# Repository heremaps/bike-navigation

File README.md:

# This repository has been archived!

The current version of the HERE WeGo app on Android does not support BLE devices anymore.

# BikeNavigation

The bike navigation project was born out of the HERE maker lab in Berlin. A group of employees volunteered their time to build a companion device that connects to the HERE app on Android, including an open-source toolkit to build a custom bike navigation device.

## License

Unless otherwise noted in `LICENSE` files for specific files or directories, the [LICENSE](LICENSE) in the root applies to all content in this repository.

## Directory Contents

* *arduino*: Codes implementing BikeNavigation BLE profile
* *ble_specs*: Documentation describing BikeNavigation BLE profile
* *board*: PCB Design files for BikeNavigation
* *enclosure*: 3d and acrylic cases for BikeNavigation

## Disclaimer

You are required to provide the end-user of the device with the following notice prior to use and are responsible to localize this notice according to local laws: “Focus on the traffic when using the device - your first consideration while using the device in traffic has to be safety.”

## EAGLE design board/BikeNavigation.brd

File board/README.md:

# BikeNavigation

## BikeNavigation PCB & schematic

The board and the schematic are designed with [CadSoft EAGLE](http://www.cadsoftusa.com/eagle-pcb-design-software/about-eagle/). To work with the files you need at least EAGLE version 6.

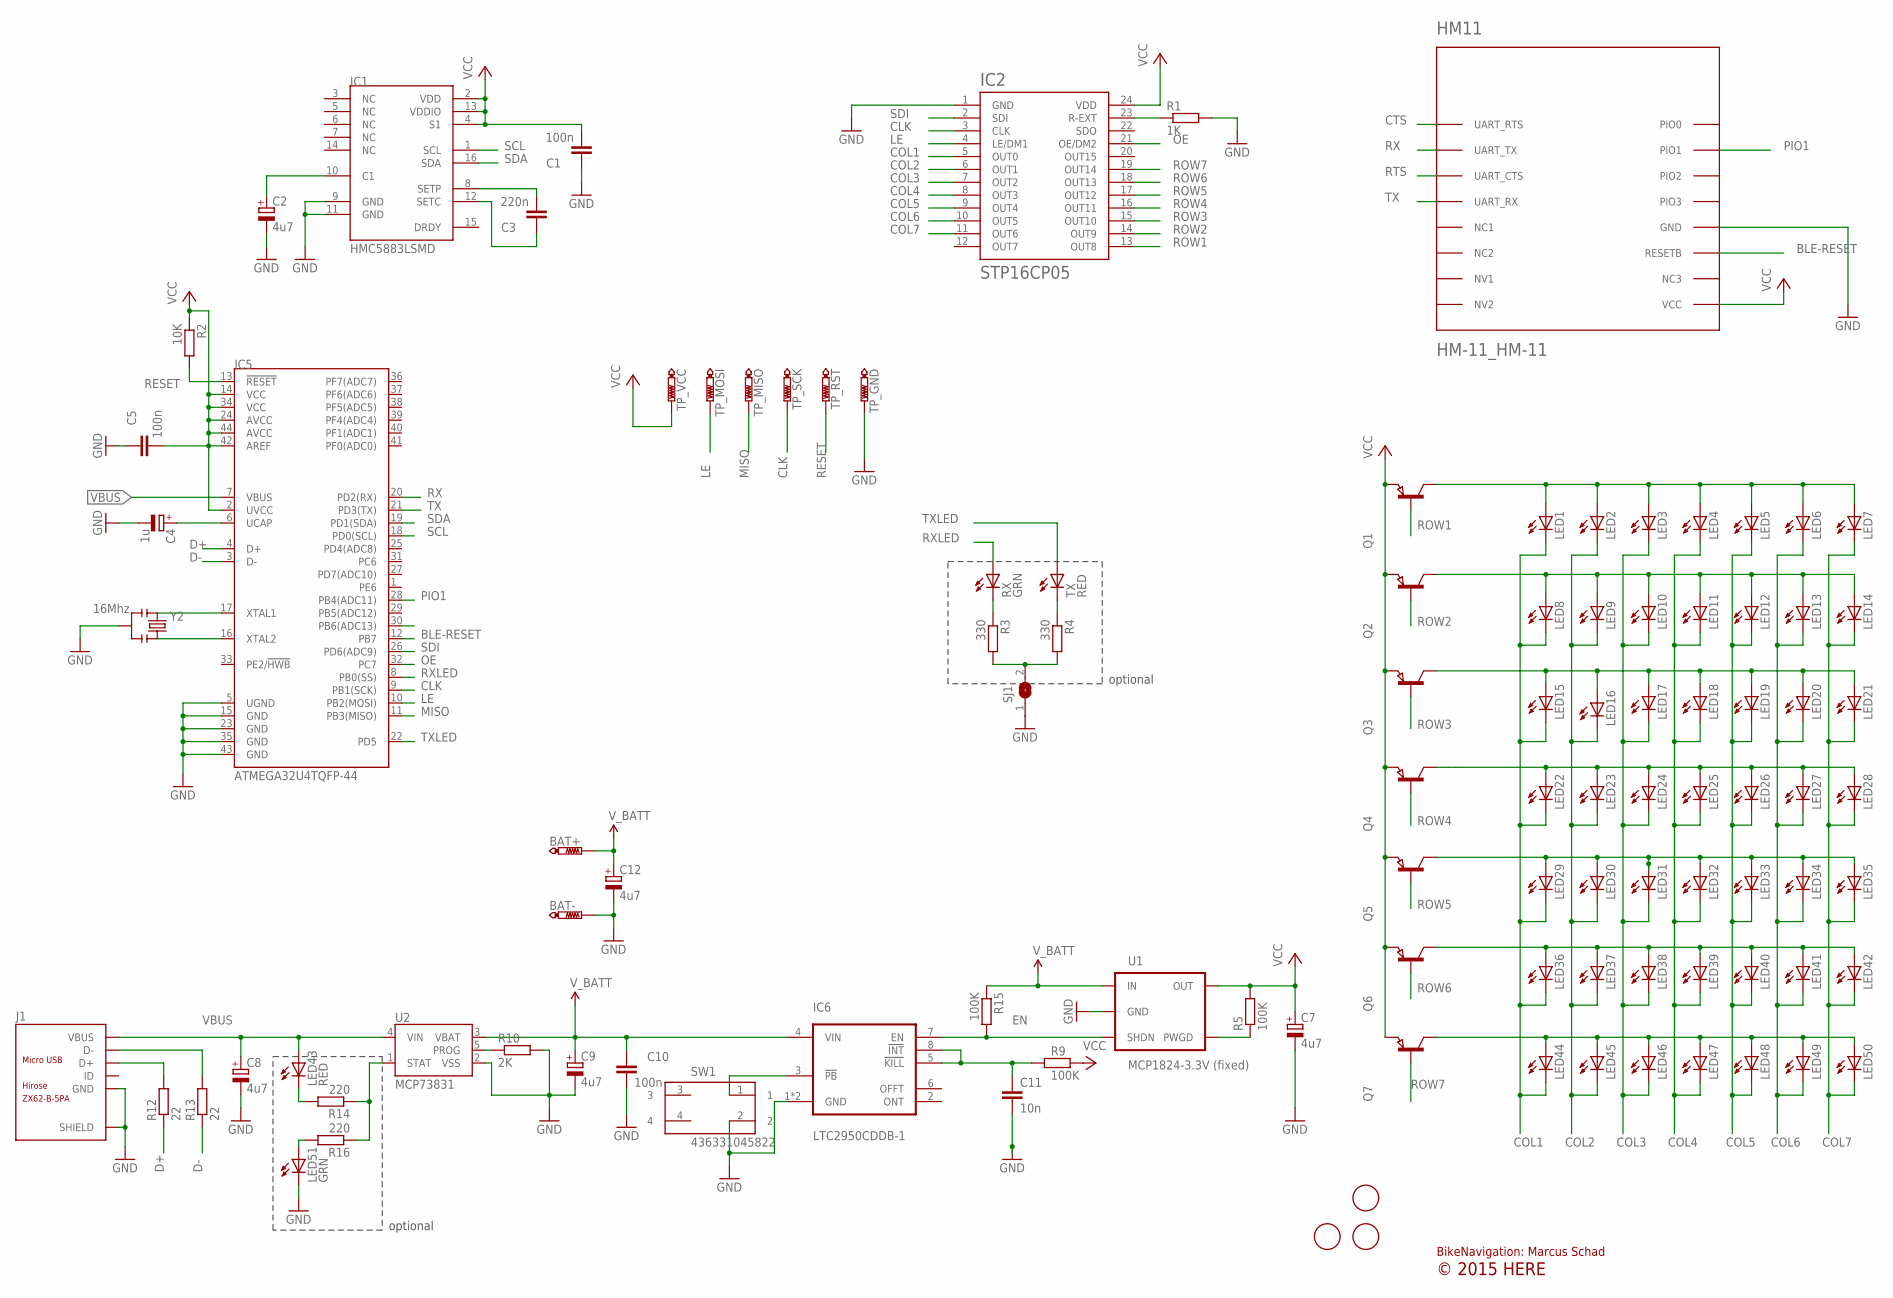
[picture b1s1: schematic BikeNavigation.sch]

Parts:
BAT+: PTR1TP20SQ; TP20SQ
BAT-: PTR1TP20SQ; TP20SQ
C1, C5, C10: 100n; C0402; PARTNO 445-3445-1-ND
C2, C7, C8, C9, C12: 4u7; SMC_A
C3: 220n; C0402; PARTNO 445-3445-1-ND
C4: 1u; SMC_A
C11: 10n; C0402; PARTNO 445-1260-1-ND
HM11: HM-11_HM-11
IC1: HMC5883LSMD; 16LPCC
IC2: STP16CP05; TSSOP24
IC5: ATMEGA32U4TQFP-44; TQFP44
IC6: LTC2950CDDB-1; DDB-8; PARTNO LTC2950IDDB-1#TRMPBFCT-ND
J1: MICRO-USB-SMD(ZX62-B-5PA); MICRO-USB5+6P-SMD-0.65-AB
LED1, LED2, LED3, LED4, LED5, LED6, LED7, LED8, LED9, LED10, LED11, LED12, LED13, LED14, LED15, LED16, LED17, LED18, LED19, LED20, LED21, LED22, LED23, LED24, LED25, LED26, LED27, LED28, LED29, LED30, LED31, LED32, LED33, LED34, LED35, LED36, LED37, LED38, LED39, LED40, LED41, LED42, LED44, LED45, LED46, LED47, LED48, LED49, LED50: LEDCHIP-LED0603; CHIP-LED0603
LED43: RED; SML0805
LED51: GRN; SML0805
Q1, Q2, Q3, Q4, Q5, Q6, Q7: PNP-TRANSISTOR_SOT23; SOT23
R1: 1K; R0402
R2: 10K; R0402
R3, R4: 330; R0402
R5: 100K; R0402
R9: 100K; R0402; PARTNO P510KJCT-ND
R10: 2K; R0402
R12, R13: 22; R0402
R14, R16: 220; R0402
R15: 100K; R0402; PARTNO P100KJCT-ND
RX: GRN; CHIP-LED0603
SJ1: SJ
SW1: 436331045822
TP_GND: PTR1TP20SQ; TP20SQ
TP_MISO: PTR1TP20SQ; TP20SQ
TP_MOSI: PTR1TP20SQ; TP20SQ
TP_RST: PTR1TP20SQ; TP20SQ
TP_SCK: PTR1TP20SQ; TP20SQ
TP_VCC: PTR1TP20SQ; TP20SQ
TX: RED; CHIP-LED0603
U1: MCP1824-3.3V (fixed); SOT23-5
U2: MCP73831; SOT23-5
U$1, U$2, U$3: FIDUCIAL; FIDUCIAL_1MM
Y2: 16Mhz; RESONATOR-SMD; PARTNO *

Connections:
$NS100: LED1.A, LED2.A, LED3.A, LED4.A, LED5.A, LED6.A, LED7.A, Q1.3 (C)
$NS101: LED8.A, LED9.A, LED10.A, LED11.A, LED12.A, LED13.A, LED14.A, Q2.3 (C)
$NS102: LED15.A, LED16.A, LED17.A, LED18.A, LED19.A, LED20.A, LED21.A, Q3.3 (C)
$NS104: LED22.A, LED23.A, LED24.A, LED25.A, LED26.A, LED27.A, LED28.A, Q4.3 (C)
$NS105: LED29.A, LED30.A, LED31.A, LED32.A, LED33.A, LED34.A, LED35.A, Q5.3 (C)
$NS107: LED36.A, LED37.A, LED38.A, LED39.A, LED40.A, LED41.A, LED42.A, Q6.3 (C)
$NS109: LED44.A, LED45.A, LED46.A, LED47.A, LED48.A, LED49.A, LED50.A, Q7.3 (C)
BLE-RESET: HM11.RESETB, IC5.12 (PB7)
CLK: IC2.3 (CLK), IC5.9 (PB1(SCK)), TP_SCK.TP
COL1: IC2.5 (OUT0), LED1.C, LED8.C, LED15.C, LED22.C, LED29.C, LED36.C, LED44.C
COL2: IC2.6 (OUT1), LED2.C, LED9.C, LED16.C, LED23.C, LED30.C, LED37.C, LED45.C
COL3: IC2.7 (OUT2), LED3.C, LED10.C, LED17.C, LED24.C, LED31.C, LED38.C, LED46.C
COL4: IC2.8 (OUT3), LED4.C, LED11.C, LED18.C, LED25.C, LED32.C, LED39.C, LED47.C
COL5: IC2.9 (OUT4), LED5.C, LED12.C, LED19.C, LED26.C, LED33.C, LED40.C, LED48.C
COL6: IC2.10 (OUT5), LED6.C, LED13.C, LED20.C, LED27.C, LED34.C, LED41.C, LED49.C
COL7: IC2.11 (OUT6), LED7.C, LED14.C, LED21.C, LED28.C, LED35.C, LED42.C, LED50.C
CTS: HM11.UART_RTS
D+: IC5.4 (D+), R12.1
D-: IC5.3 (D-), R13.1
EN: IC6.7 (EN), R15.2, U1.3 (SHDN)
GND: BAT-.TP, C1.1, C2.-, C4.-, C5.1, C7.-, C8.-, C9.-, C10.2, C11.2, C12.-, HM11.GND, IC1.9 (GND), IC1.11 (GND), IC2.1 (GND), IC5.5 (UGND), IC5.15 (GND), IC5.23 (GND), IC5.35 (GND), IC5.43 (GND), IC6.1 (GND), IC6.TPAD (GND), J1.5 (GND), J1.P1 (SHIELD), J1.P2 (SHIELD), J1.P3 (SHIELD), J1.P4 (SHIELD), J1.P5 (SHIELD), J1.P6 (SHIELD), LED51.C, R1.2, R10.2, SJ1.1, SW1.2, TP_GND.TP, U1.2 (GND), U2.2 (VSS), Y2.2
LE: IC2.4 (LE/DM1), IC5.10 (PB2(MOSI)), TP_MOSI.TP
MISO: IC5.11 (PB3(MISO)), TP_MISO.TP
unnamed: R5.1, U1.4 (PWGD)
unnamed: R3.1, RX.C
unnamed: R4.1, TX.C
unnamed: IC2.23 (R-EXT), R1.1
unnamed: R3.2, R4.2, SJ1.2
unnamed: C4.+, IC5.6 (UCAP)
unnamed: LED43.C, R14.2
unnamed: LED51.A, R16.2
unnamed: J1.3 (D+), R12.2
unnamed: C2.+, IC1.10 (C1)
unnamed: J1.2 (D-), R13.2
unnamed: IC6.3 (!PB), SW1.1
unnamed: C11.1, IC6.5 (!KILL), IC6.8 (!INT), R9.1
unnamed: C3.2, IC1.8 (SETP)
unnamed: C3.1, IC1.12 (SETC)
OE: IC2.21 (OE/DM2), IC5.32 (PC7)
PIO1: HM11.PIO1, IC5.28 (PB4(ADC11))
PROG: R10.1, U2.5 (PROG)
RESET: IC5.13 (!RESET), R2.2, TP_RST.TP
ROW1: IC2.13 (OUT8), Q1.1 (B)
ROW2: IC2.14 (OUT9), Q2.1 (B)
ROW3: IC2.15 (OUT10), Q3.1 (B)
ROW4: IC2.16 (OUT11), Q4.1 (B)
ROW5: IC2.17 (OUT12), Q5.1 (B)
ROW6: IC2.18 (OUT13), Q6.1 (B)
ROW7: IC2.19 (OUT14), Q7.1 (B)
RTS: HM11.UART_CTS
RX: HM11.UART_TX, IC5.20 (PD2(RX))
RXLED: IC5.8 (PB0(SS)), RX.A
SCL: IC1.1 (SCL), IC5.18 (PD0(SCL))
SDA: IC1.16 (SDA), IC5.19 (PD1(SDA))
SDI: IC2.2 (SDI), IC5.26 (PD6(ADC9))
STAT: R14.1, R16.1, U2.1 (STAT)
TX: HM11.UART_RX, IC5.21 (PD3(TX))
TXLED: IC5.22 (PD5), TX.A
VBUS: C8.+, IC5.7 (VBUS), J1.1 (VBUS), LED43.A, U2.4 (VIN)
VCC: C1.2, C5.2, C7.+, HM11.VCC, IC1.2 (VDD), IC1.4 (S1), IC1.13 (VDDIO), IC2.24 (VDD), IC5.2 (UVCC), IC5.14 (VCC), IC5.24 (AVCC), IC5.34 (VCC), IC5.42 (AREF), IC5.44 (AVCC), Q1.2 (E), Q2.2 (E), Q3.2 (E), Q4.2 (E), Q5.2 (E), Q6.2 (E), Q7.2 (E), R2.1, R5.2, R9.2, TP_VCC.TP, U1.5 (OUT)
V_BATT: BAT+.TP, C9.+, C10.1, C12.+, IC6.4 (VIN), R15.1, U1.1 (IN), U2.3 (VBAT)
XTAL1: IC5.17 (XTAL1), Y2.1
XTAL2: IC5.16 (XTAL2), Y2.3

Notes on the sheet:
BikeNavigation: Marcus Schad
optional
© 2015 HERE

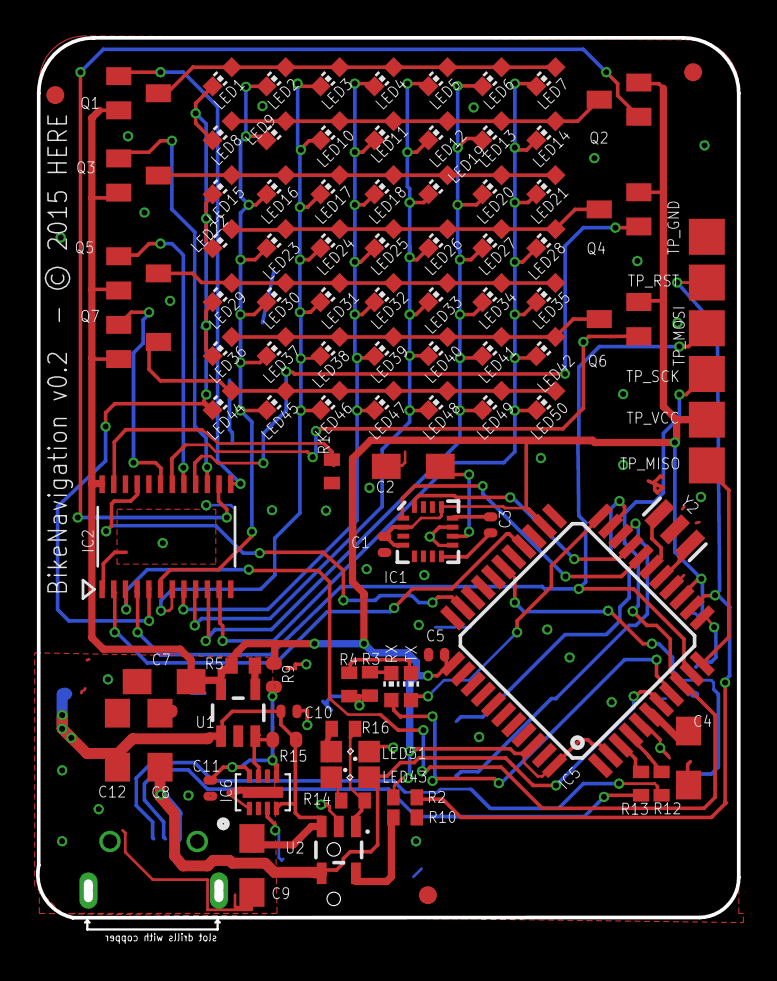
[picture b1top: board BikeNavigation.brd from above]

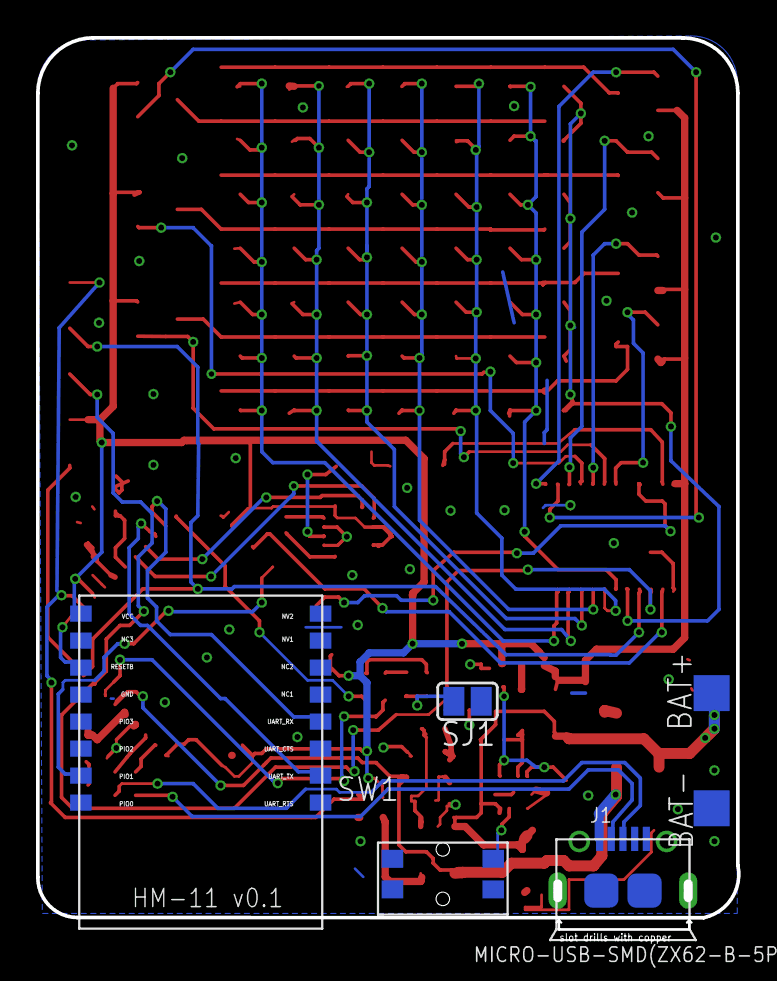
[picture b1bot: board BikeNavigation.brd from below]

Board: 2 copper layers, 38.9 x 49.5 mm, 105 parts (6 on the bottom side), 61 nets.

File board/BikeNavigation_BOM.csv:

"Qty";"Value";"Device";"Package";"Parts";"Description";"PARTNO";"PROD_ID";"TP_SIGNAL_NAME";
"49";"";"LEDCHIP-LED0603";"CHIP-LED0603";"LED1, LED2, LED3, LED4, LED5, LED6, LED7, LED8, LED9, LED10, LED11, LED12, LED13, LED14, LED15, LED16, LED17, LED18, LED19, LED20, LED21, LED22, LED23, LED24, LED25, LED26, LED27, LED28, LED29, LED30, LED31, LED32, LED33, LED34, LED35, LED36, LED37, LED38, LED39, LED40, LED41, LED42, LED44, LED45, LED46, LED47, LED48, LED49, LED50";"LED";"";"";"";
"7";"";"PNP-TRANSISTOR_SOT23";"SOT23";"Q1, Q2, Q3, Q4, Q5, Q6, Q7";"PNP TRANSISTOR";"";"";"";
"1";"";"SJ";"SJ";"SJ1";"SMD solder JUMPER";"";"";"";
"1";"100K";"R-EU_R0402";"R0402";"R5";"RESISTOR, European symbol";"";"";"";
"1";"100K";"R-EU_R0402";"R0402";"R15";"RESISTOR, European symbol";"P100KJCT-ND";"";"";
"1";"100K";"R-EU_R0402";"R0402";"R9";"RESISTOR, European symbol";"P510KJCT-ND";"";"";
"3";"100n";"C-EUC0402";"C0402";"C1, C5, C10";"CAPACITOR, European symbol";"445-3445-1-ND";"";"";
"1";"10K";"R-EU_R0402";"R0402";"R2";"RESISTOR, European symbol";"";"";"";
"1";"10n";"C-EUC0402";"C0402";"C11";"CAPACITOR, European symbol";"445-1260-1-ND";"";"";
"1";"16Mhz";"RESONATORSMD";"RESONATOR-SMD";"Y2";"Resonator";"*";"";"";
"1";"1K";"R-EU_R0402";"R0402";"R1";"RESISTOR, European symbol";"";"";"";
"1";"1u";"CPOL-EUSMCA";"SMC_A";"C4";"POLARIZED CAPACITOR, European symbol";"";"";"";
"2";"22";"R-EU_R0402";"R0402";"R12, R13";"RESISTOR, European symbol";"";"";"";
"2";"220";"R-EU_R0402";"R0402";"R14, R16";"RESISTOR, European symbol";"";"";"";
"1";"220n";"C-EUC0402";"C0402";"C3";"CAPACITOR, European symbol";"445-3445-1-ND";"";"";
"1";"2K";"R-EU_R0402";"R0402";"R10";"RESISTOR, European symbol";"";"";"";
"2";"330";"R-EU_R0402";"R0402";"R3, R4";"RESISTOR, European symbol";"";"";"";
"1";"436331045822";"436331045822";"436331045822";"SW1";"WS-TUS-3.5x4.7 mm side push SMD Tact Switch with boss design, 4 pins";"";"";"";
"5";"4u7";"CPOL-EUSMCA";"SMC_A";"C2, C7, C8, C9, C12";"POLARIZED CAPACITOR, European symbol";"";"";"";
"1";"ATMEGA32U4TQFP-44";"ATMEGA32U4TQFP-44";"TQFP44";"IC5";"Atmel 44-pin 8-bit Microcontroller with 32KBytes of ISP Flash and USB Controller";"";"";"";
"3";"FIDUCIAL";"FIDUCIAL";"FIDUCIAL_1MM";"U$1, U$2, U$3";"For use by pick and place machines to calibrate the vision/machine, 1mm";"";"";"";
"1";"GRN";"LEDCHIP-LED0603";"CHIP-LED0603";"RX";"LED";"";"";"";
"1";"GRN";"LEDSML0805";"SML0805";"LED51";"LED";"";"";"";
"1";"HM-11_HM-11";"HM-11_HM-11";"HM-11_HM-11";"HM11";"";"";"";"";
"1";"HMC5883LSMD";"HMC5883LSMD";"16LPCC";"IC1";"3 Axis Digital Compass IC";"";"IC-10284";"";
"1";"LTC2950CDDB-1";"LTC2950-1DFN(3X2)";"DDB-8";"IC6";"LTC2950-1  Push button ON/OFF Controler  LINEAR TECHNOLOGY";"LTC2950IDDB-1#TRMPBFCT-ND";"";"";
"1";"MCP1824-3.3V (fixed)";"V_REG_LDOSMD";"SOT23-5";"U1";"Voltage Regulator LDO";"";"";"";
"1";"MCP73831";"MCP73831";"SOT23-5";"U2";"Miniature single cell, fully integrated Li-Ion, Li-polymer charge management controller";"";"IC-09995";"";
"1";"MICRO-USB-SMD(ZX62-B-5PA)";"MICRO-USB-SMD(ZX62-B-5PA)";"MICRO-USB5+6P-SMD-0.65-AB";"J1";"320010005";"";"";"";
"8";"PTR1TP20SQ";"PTR1TP20SQ";"TP20SQ";"BAT+, BAT-, TP_GND, TP_MISO, TP_MOSI, TP_RST, TP_SCK, TP_VCC";"TEST PIN";"";"";"";
"1";"RED";"LEDCHIP-LED0603";"CHIP-LED0603";"TX";"LED";"";"";"";
"1";"RED";"LEDSML0805";"SML0805";"LED43";"LED";"";"";"";
"1";"STP16CP05";"STP16CP05";"TSSOP24";"IC2";"";"";"";"";

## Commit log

2015-10-24 Fixed display of tabular data
    There must be at least 3 dashes separating each header cell
2015-10-28 Arduino code: mirroring of icons was added to save RAM. Only right-sided icons are stored, left-side are shown by mirroring right-side icons.
2015-11-04 Fix the LED driver IC designation in the board file
    Change it to correct "IC2" instead of incorrect and
    duplicate "IC1". Thanks to @dwlocks for reporting.
    Closes: #2
2015-11-08 Added usage statement to the script generating c++ code from Led Matrix Studio output; Renamed the script generating c++ code from Led Matrix Studio output; Added some comments to the Arduino code; A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
2015-11-08 Removed not related or outdated files
2015-11-08 Added current set of LED patterns
2015-11-19 Remove serial monitor #define
    Move C++ code inside a folder matching the Arduino sketch name. The IDE is
    picky about this.
2015-11-19 Use the right type for the baud rate
    Remove some logging.
2016-01-12 Removing `initialized` flag
    Setting variable `initialized` at the end of `setup()` is redundant as `setup()` is guaranteed to run before anything else.
2016-02-01 Clean up the license terms and copyright statements
    Put license terms into separate LICENSE files for easier lookup. Inline
    the CC BY-SA 4.0 license text instead of just linking to it. Reformat
    license texts to extactly match what GitHub adds when using the license
    selector from its web interface.
2016-05-12 README: Use the exact directory names when describing their contents
2016-05-12 README: Improve esp. the usage formatting
2016-06-10 Change the Copyright holder to HERE Europe B.V.
2016-08-03 no need to escape underscores
    also changed parameter "outname" to "varname" to avoid misunderstandings - the output is not written to a file, a variable is written to stdout.
2016-11-07 Consolidate the CC-BY-SA LICENSE files into the root LICENSE file
    Also, use the full license text so it gets properly detected and shown in
    the GitHub web interface.
2018-03-28 removed waiting after Wire.requestFrom(). fixes #14

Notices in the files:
board/BikeNavigation.brd:
BikeNavigation v0.2  - © 2015 HERE
parts and their libraries:
SparkFun-PowerIC: Licensing: Creative Commons ShareAlike 4.0 International - https://creativecommons.org/licenses/by-sa/4.0
Kurzhubtaster: Copyright: Würth Elektronik
